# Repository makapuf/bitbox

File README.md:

bitbox
======

This is the core project for revision 2 bitbox.

Bitbox is a 32bit open hardware/source DIY console based on a unique chip (a cortex m4 with 1MB flash and 192k RAM).
It has 2 USB devices input, stereo sound output, micro SD card, VGA graphics up to 800x600 @ 32k colors. On the software side, a bootloader, simulators and several games, emulators and libraries.

Also the hardware is included here.

More info on [the development blog](http://bitboxconsole.blogspot.com)

Information can be found on [the project wiki](https://github.com/makapuf/bitbox/wiki)

You can also hop on the mailing list : bitbox-console@googlegroups.com  / https://groups.google.com/forum/#!forum/bitbox-console

Other repos
=========

This repository include the base SDK and some examples. There are other repos on github however: 

 * [A jumper game](https://github.com/makapuf/bitbox-jump)
 * [A GameBoy emulator](https://github.com/makapuf/bitboy)
 * [A ZX Spectrum 48 emulator](https://github.com/makapuf/bitbox-spectrum)
 * [Another game](https://github.com/makapuf/bitbox-polar)
 * [A sound toy / Rhythm box](https://github.com/makapuf/beatblocks)
 * [beam racer - a car game (WIP)](https://github.com/pulkomandy/beamracer_btbx)
 
... and many more ! See [the software index](https://github.com/makapuf/bitbox/wiki/Software-Index) on the wiki
makapuf

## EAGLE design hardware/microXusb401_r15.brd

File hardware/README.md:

hardware schematics and board licensed under the CC BY SA NC license.
please contact me for commercial uses

makapuf2@gmail.com

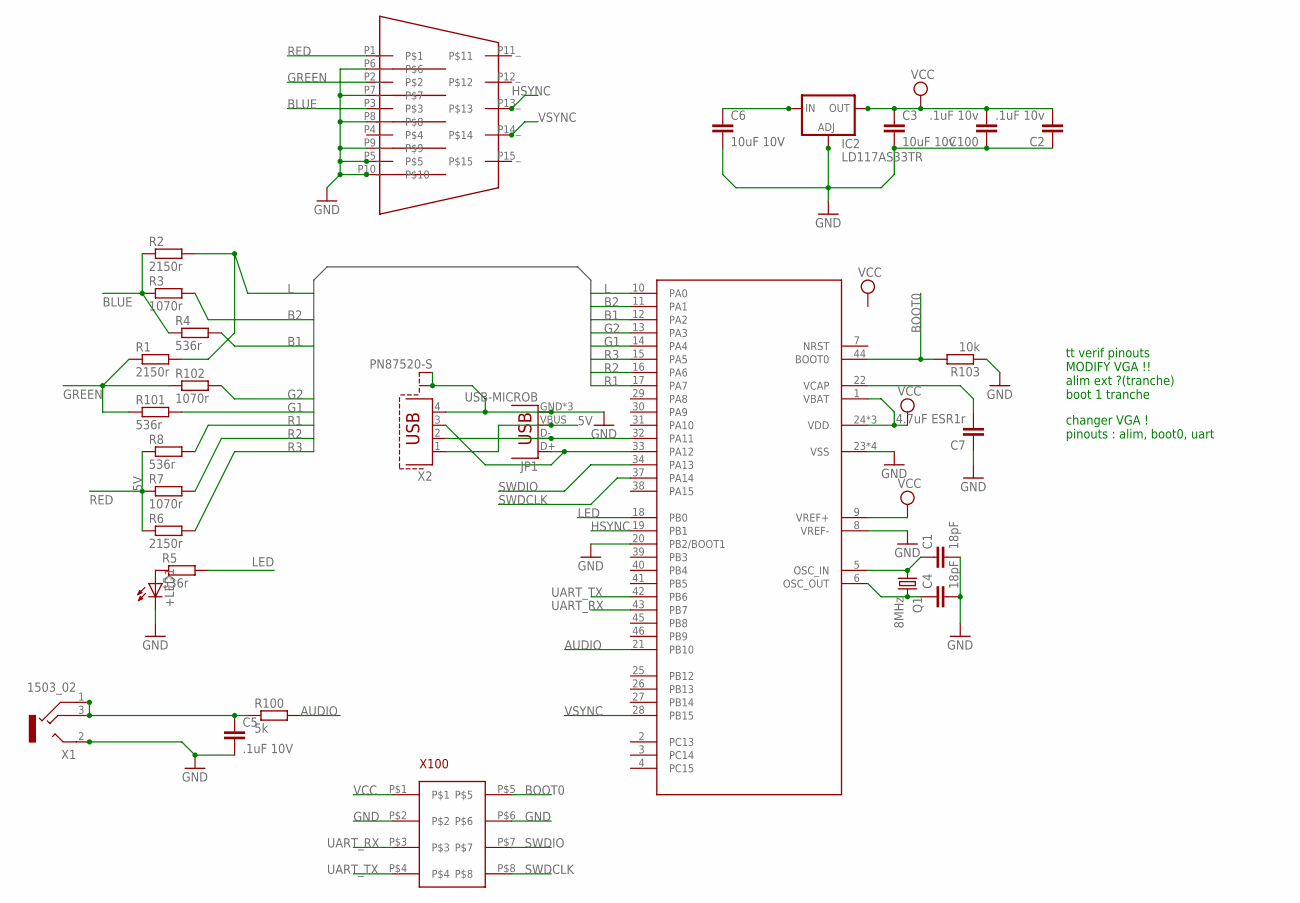
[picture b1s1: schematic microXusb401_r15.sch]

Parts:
+LED1: LEDCHIPLED_0805; CHIPLED_0805
C1, C4: 18pF; C1608
C2, C100: .1uF 10v; C1608
C3: 10uF 10v; C1608
C5: .1uF 10V; C1608
C6: 10uF 10V; C1608
C7: 4.7uF ESR1r; C1608
CON1: VGA_GTK_USLIM; VGA_SLIM3
IC1: STM32F401CCUQFN48_B; QFN-48
IC2: LD117AS33TR; SOT223
JP1: USB-MICROB
Q1: 8MHz; SM49
R1, R2, R6: 2150r; R0603
R3, R7, R102: 1070r; R0603
R4, R5, R8, R101: 536r; R0603
R100: 5k; R0603
R103: 10k; R0603
X1: 1503_02
X2: PN87520-S
X100: HEADER_BORDER_4X2

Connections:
5V: C6.1, IC2.3 (IN), JP1.VBUS, X2.1
AUDIO: IC1.21 (PB10), R100.2
B1: IC1.12 (PA2), R4.2
B2: IC1.11 (PA1), R3.2
BLUE: CON1.P3_, R2.1, R3.1, R4.1
BOOT0: IC1.44 (BOOT0), R103.2, X100.P$5
G1: IC1.14 (PA4), R101.2
G2: IC1.13 (PA3), R102.2
GND: +LED1.C, C1.2, C2.1, C3.2, C4.2, C5.2, C6.2, C7.1, C100.1, CON1.P5_, CON1.P6_, CON1.P7_, CON1.P8_, CON1.P9_, CON1.P10_, IC1.8 (VREF-), IC1.20 (PB2/BOOT1), IC1.23 (VSS), IC1.35 (VSS), IC1.47 (VSS), IC1.EXP (VSS), IC2.1 (ADJ), JP1.GND, JP1.MT1 (GND), JP1.MT2 (GND), R103.1, X1.2, X2.4, X2.S1, X2.S2, X100.P$2, X100.P$6
GREEN: CON1.P2_, R1.1, R101.1, R102.1
HSYNC: CON1.P13_, IC1.19 (PB1)
L: IC1.10 (PA0), R1.2, R2.2
LED: IC1.18 (PB0), R5.2
unnamed: IC1.33 (PA12), JP1.D+, X2.3
unnamed: IC1.32 (PA11), JP1.D-, X2.2
unnamed: C7.2, IC1.22 (VCAP)
unnamed: C5.1, R100.1, X1.1, X1.3
unnamed: +LED1.A, R5.1
unnamed: C1.1, IC1.5 (OSC_IN), Q1.1
unnamed: C4.1, IC1.6 (OSC_OUT), Q1.2
R1: IC1.17 (PA7), R8.2
R2: IC1.16 (PA6), R7.2
R3: IC1.15 (PA5), R6.2
RED: CON1.P1_, R6.1, R7.1, R8.1
SWDCLK: IC1.37 (PA14), X100.P$8
SWDIO: IC1.34 (PA13), X100.P$7
UART_RX: IC1.43 (PB7), X100.P$3
UART_TX: IC1.42 (PB6), X100.P$4
VCC: C2.2, C3.1, C100.2, IC1.1 (VBAT), IC1.9 (VREF+), IC1.24 (VDD), IC1.36 (VDD), IC1.48 (VDD), IC2.4 (OUT), X100.P$1
VSYNC: CON1.P14_, IC1.28 (PB15)

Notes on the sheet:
changer VGA ! pinouts : alim, boot0, uart
tt verif pinouts MODIFY VGA !! alim ext ?(tranche) boot 1 tranche

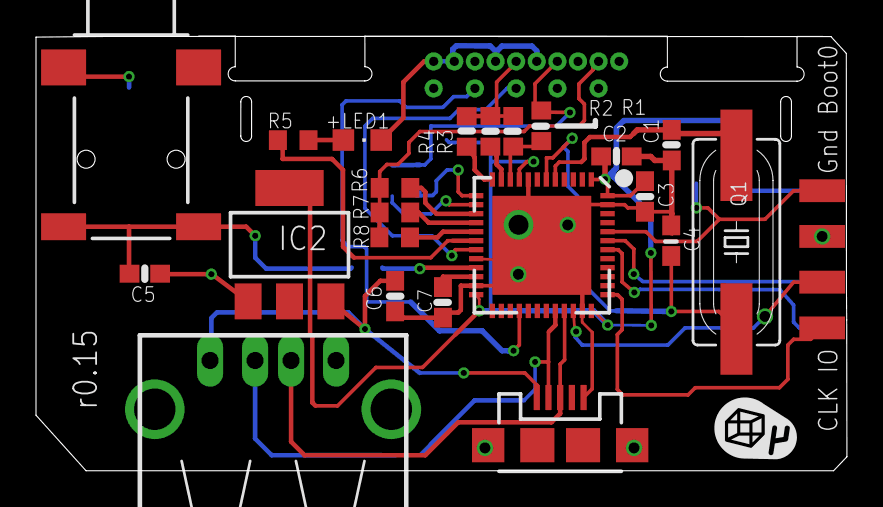
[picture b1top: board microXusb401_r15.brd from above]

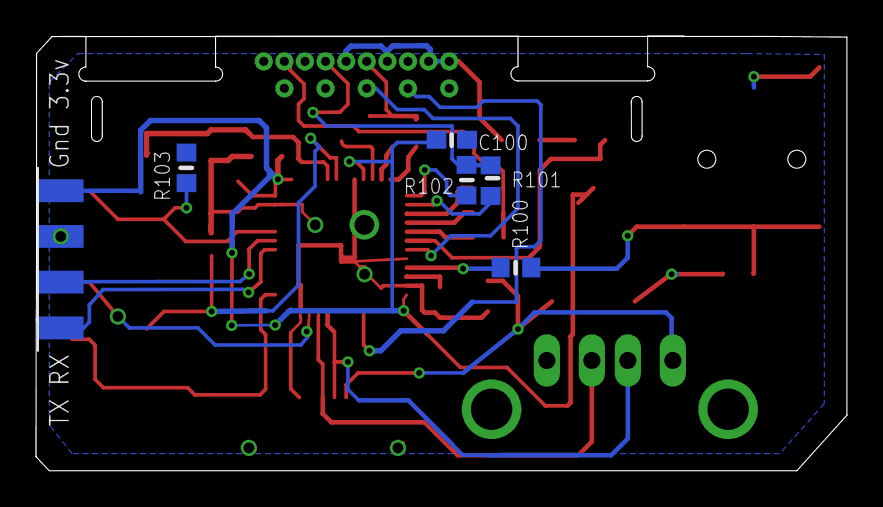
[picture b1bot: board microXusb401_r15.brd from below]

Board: 2 copper layers, 45.0 x 24.1 mm, 29 parts (6 on the bottom side), 30 nets.

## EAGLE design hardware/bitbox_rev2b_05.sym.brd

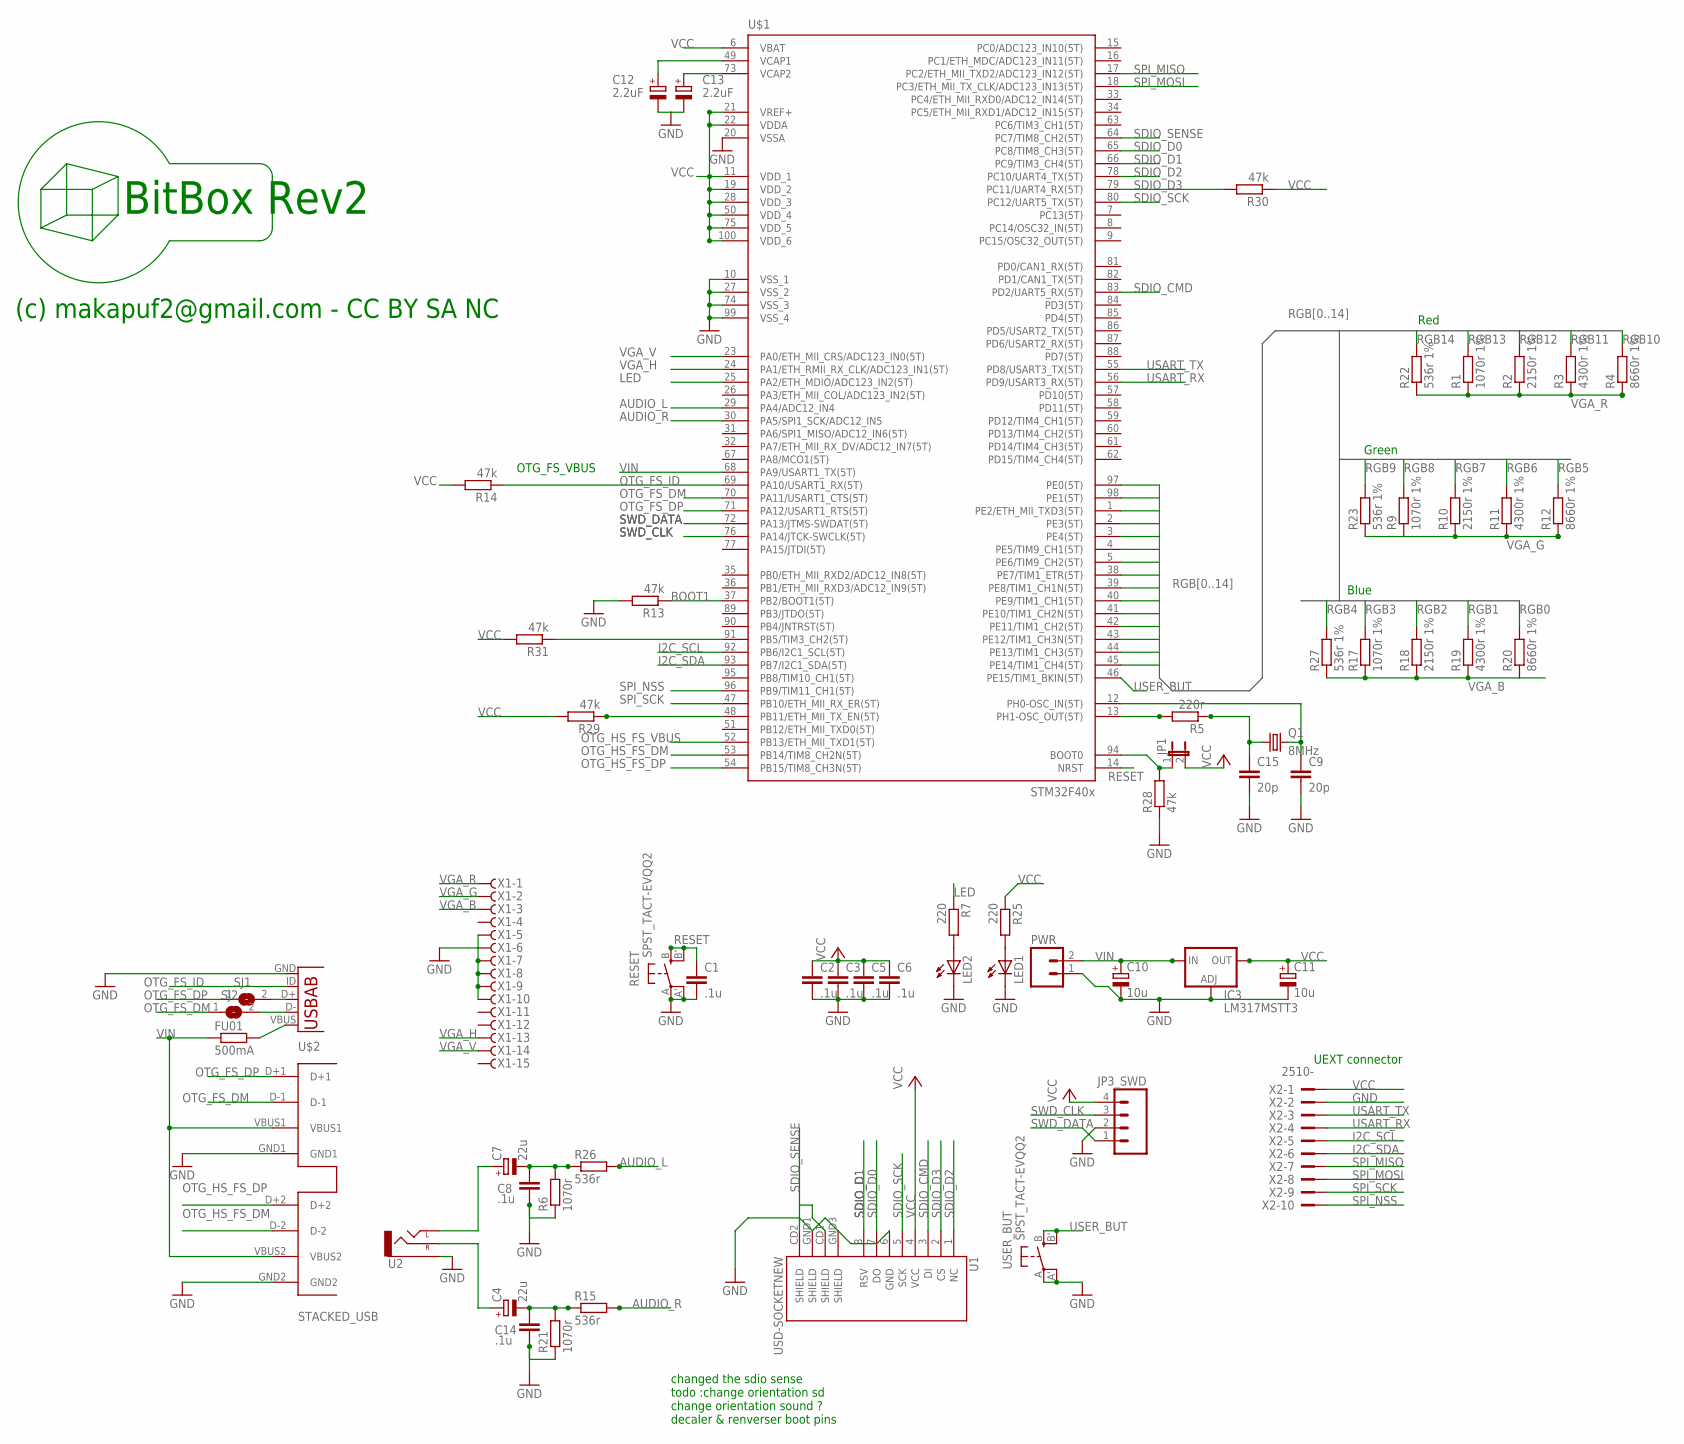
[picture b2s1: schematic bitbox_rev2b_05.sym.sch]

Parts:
C1, C2, C3, C5, C6, C8, C14: .1u; C0603
C4, C7: 22u; 153CLV-0505
C9, C15: 20p; C0603
C10, C11: 10u; SMC_A
C12, C13: 2.2uF; SMC_A
FU01: 500mA; R1206
IC3: LM317MSTT3; SOT223
JP1: JP1E; JP1
JP3_SWD: M04PTH; 1X04
LED1, LED2: LEDCHIPLED_0805; CHIPLED_0805
PWR: M02PTH; 1X02
Q1: 8MHz; SM49
R1, R9, R17: 1070r 1%; R0603
R2, R10, R18: 2150r 1%; R0603
R3, R11, R19: 4300r 1%; R0603
R4, R12, R20: 8660r 1%; R0603
R5: 220r; R0603
R6, R21: 1070r; R0603
R7, R25: 220; R0603
R13, R14, R28, R29, R30, R31: 47k; R0603
R15, R26: 536r; R0603
R22, R23, R27: 536r 1%; R0603
RESET: SPST_TACT-EVQQ2; EVQ-Q2
SJ1, SJ2: SJ
U1: USD-SOCKETNEW; MICRO-SD-SOCKET-PP
U2: AUDIO-JACKPTH; AUDIO-JACK
U3: USB-AB; USB-AB-MICRO-SMD
U$1: STM32F407V; TQFP100
U$2: STACKED_USB; 2STACKED
USER_BUT: SPST_TACT-EVQQ2; EVQ-Q2
X1: HF15HS; HDF15H
X2: 2510-; PAK100/2500-10

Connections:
AUDIO_L: R26.2, U$1.29 (PA4/ADC12_IN4)
AUDIO_R: R15.2, U$1.30 (PA5/SPI1_SCK/ADC12_IN5)
BOOT1: R13.1, U$1.37 (PB2/BOOT1(5T))
GND: C1.2, C2.2, C3.2, C5.2, C6.2, C8.2, C9.2, C10.-, C11.-, C12.-, C13.-, C14.2, C15.2, IC3.1 (ADJ), JP3_SWD.2, LED1.C, LED2.C, PWR.1, R6.1, R13.2, R21.1, R28.1, RESET.A, RESET.A' (P1), U1.6 (GND), U1.GND1 (SHIELD), U1.GND3 (SHIELD), U2.SLEEVE, U3.GND, U$1.10 (VSS_1), U$1.20 (VSSA), U$1.27 (VSS_2), U$1.74 (VSS_3), U$1.99 (VSS_4), U$2.GND1, U$2.GND2, USER_BUT.A, USER_BUT.A' (P1), X1.5, X1.6, X1.7, X1.8, X1.9, X1.10, X2.2
I2C_SCL: U$1.92 (PB6/I2C1_SCL(5T)), X2.5
I2C_SDA: U$1.93 (PB7/I2C1_SDA(5T)), X2.6
LED: R7.1, U$1.25 (PA2/ETH_MDIO/ADC123_IN2(5T))
unnamed: LED2.A, R7.2
unnamed: C13.+, U$1.73 (VCAP2)
unnamed: C7.+, U2.TIP (LEFT)
unnamed: C12.+, U$1.49 (VCAP1)
unnamed: SJ1.2, U3.D+
unnamed: C15.1, Q1.1, R5.1
unnamed: C9.1, Q1.2, U$1.12 (PH0-OSC_IN(5T))
unnamed: C4.-, C14.1, R15.1, R21.2
unnamed: C7.-, C8.1, R6.2, R26.1
unnamed: C4.+, U2.RING (RIGHT)
unnamed: FU01.2, U3.VBUS
unnamed: SJ2.2, U3.D-
unnamed: R31.1, U$1.91 (PB5/TIM3_CH2(5T))
unnamed: LED1.A, R25.2
unnamed: R5.2, U$1.13 (PH1-OSC_OUT(5T))
unnamed: JP1.1, R28.2, U$1.94 (BOOT0)
OTG_FS_DM: SJ2.1, U$1.70 (PA11/USART1_CTS(5T)), U$2.D-1
OTG_FS_DP: SJ1.1, U$1.71 (PA12/USART1_RTS(5T)), U$2.D+1
OTG_FS_ID: R14.1, U3.ID (USBID), U$1.69 (PA10/USART1_RX(5T))
OTG_HS_FS_DM: U$1.53 (PB14/TIM8_CH2N(5T)), U$2.D-2
OTG_HS_FS_DP: U$1.54 (PB15/TIM8_CH3N(5T)), U$2.D+2
OTG_HS_FS_VBUS: U$1.52 (PB13/ETH_MII_TXD1(5T))
RESET: C1.1, RESET.B (S), RESET.B' (S1), U$1.14 (NRST)
RGB0: R20.2, U$1.97 (PE0(5T))
RGB1: R19.2, U$1.98 (PE1(5T))
RGB2: R18.2, U$1.1 (PE2/ETH_MII_TXD3(5T))
RGB3: R17.2, U$1.2 (PE3(5T))
RGB4: R27.2, U$1.3 (PE4(5T))
RGB5: R12.2, U$1.4 (PE5/TIM9_CH1(5T))
RGB6: R11.2, U$1.5 (PE6/TIM9_CH2(5T))
RGB7: R10.2, U$1.38 (PE7/TIM1_ETR(5T))
RGB8: R9.2, U$1.39 (PE8/TIM1_CH1N(5T))
RGB9: R23.2, U$1.40 (PE9/TIM1_CH1(5T))
RGB10: R4.2, U$1.41 (PE10/TIM1_CH2N(5T))
RGB11: R3.2, U$1.42 (PE11/TIM1_CH2(5T))
RGB12: R2.2, U$1.43 (PE12/TIM1_CH3N(5T))
RGB13: R1.2, U$1.44 (PE13/TIM1_CH3(5T))
RGB14: R22.2, U$1.45 (PE14/TIM1_CH4(5T))
SDIO_CMD: U1.3 (DI), U$1.83 (PD2/UART5_RX(5T))
SDIO_D0: U1.7 (DO), U$1.65 (PC8/TIM8_CH3(5T))
SDIO_D1: U1.8 (RSV), U$1.66 (PC9/TIM3_CH4(5T))
SDIO_D2: U1.1 (NC), U$1.78 (PC10/UART4_TX(5T))
SDIO_D3: R30.2, U1.2 (CS), U$1.79 (PC11/UART4_RX(5T))
SDIO_SCK: U1.5 (SCK), U$1.80 (PC12/UART5_TX(5T))
SDIO_SENSE: U1.CD1 (SHIELD), U1.CD2 (SHIELD), U$1.64 (PC7/TIM8_CH2(5T))
SPI_MISO: U$1.17 (PC2/ETH_MII_TXD2/ADC123_IN12(5T)), X2.7
SPI_MOSI: U$1.18 (PC3/ETH_MII_TX_CLK/ADC123_IN13(5T)), X2.8
SPI_NSS: U$1.96 (PB9/TIM11_CH1(5T)), X2.10
SPI_SCK: U$1.47 (PB10/ETH_MII_RX_ER(5T)), X2.9
SWD_CLK: JP3_SWD.3, U$1.76 (PA14/JTCK-SWCLK(5T))
SWD_DATA: JP3_SWD.1, U$1.72 (PA13/JTMS-SWDAT(5T))
USART_RX: U$1.56 (PD9/USART3_RX(5T)), X2.4
USART_TX: U$1.55 (PD8/USART3_TX(5T)), X2.3
USER_BUT: U$1.46 (PE15/TIM1_BKIN(5T)), USER_BUT.B (S), USER_BUT.B' (S1)
VCC: C2.1, C3.1, C5.1, C6.1, C11.+, IC3.4 (OUT), JP1.2, JP3_SWD.4, R14.2, R25.1, R29.2, R30.1, R31.2, U1.4 (VCC), U$1.6 (VBAT), U$1.11 (VDD_1), U$1.19 (VDD_2), U$1.21 (VREF+), U$1.22 (VDDA), U$1.28 (VDD_3), U$1.50 (VDD_4), U$1.75 (VDD_5), U$1.100 (VDD_6), X2.1
VGA_B: R17.1, R18.1, R19.1, R20.1, R27.1, X1.3
VGA_G: R9.1, R10.1, R11.1, R12.1, R23.1, X1.2
VGA_H: U$1.24 (PA1/ETH_RMII_RX_CLK/ADC123_IN1(5T)), X1.13
VGA_R: R1.1, R2.1, R3.1, R4.1, R22.1, X1.1
VGA_V: U$1.23 (PA0/ETH_MII_CRS/ADC123_IN0(5T)), X1.14
VIN: C10.+, FU01.1, IC3.3 (IN), PWR.2, U$1.68 (PA9/USART1_TX(5T)), U$2.VBUS1, U$2.VBUS2
YYY: R29.1, U$1.48 (PB11/ETH_MII_TX_EN(5T))

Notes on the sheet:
Red
Green
Blue
UEXT connector
OTG_FS_VBUS
BitBox Rev2
(c) makapuf2@gmail.com - CC BY SA NC
changed the sdio sense todo :change orientation sd change orientation sound ? decaler & renverser boot pins

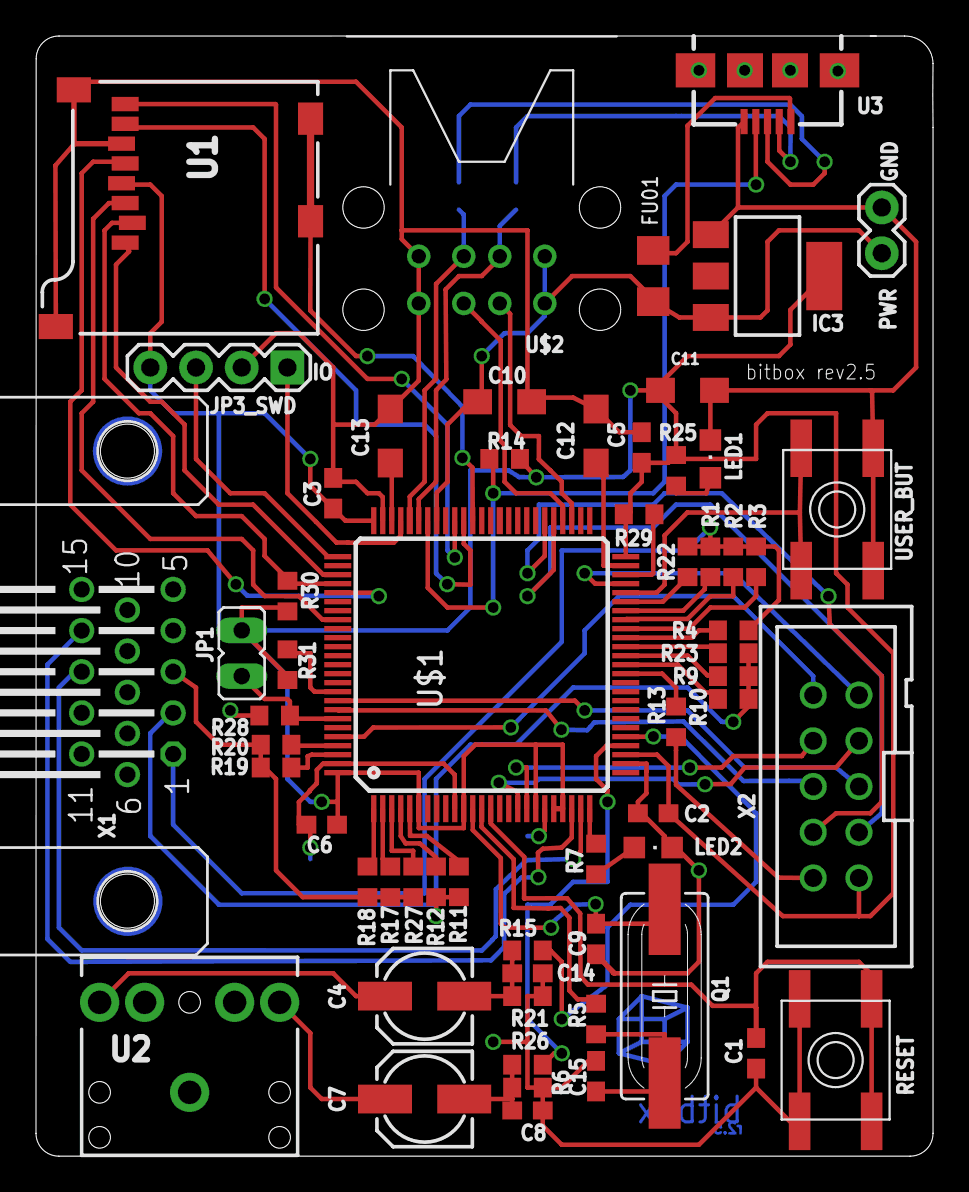
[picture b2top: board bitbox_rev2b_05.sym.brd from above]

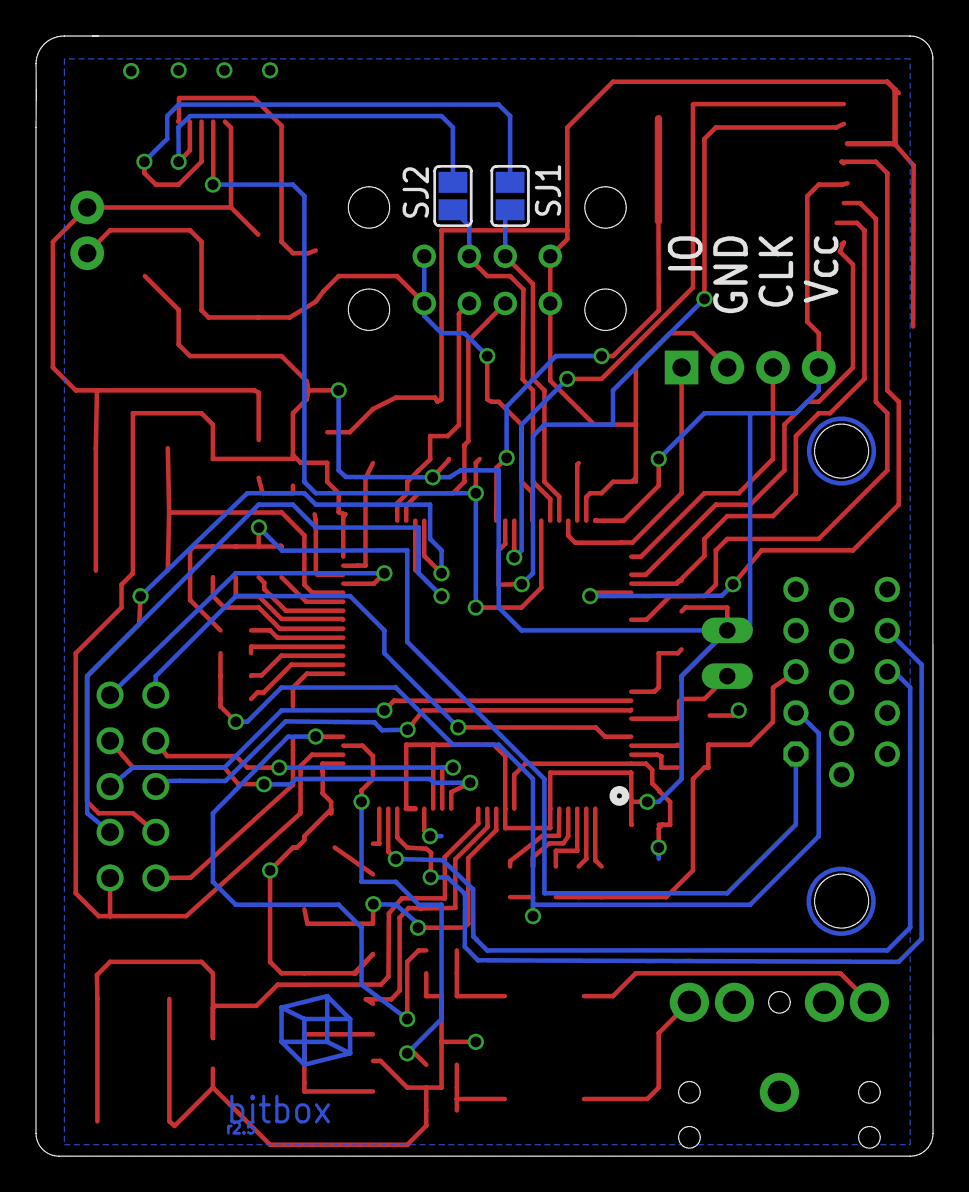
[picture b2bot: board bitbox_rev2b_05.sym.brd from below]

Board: 2 copper layers, 49.8 x 62.2 mm, 62 parts (2 on the bottom side), 68 nets.

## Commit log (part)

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2015-12-14 test_sdio readme
2015-12-14 fix remove song if not exist in test_chip
2015-12-14 re-added rcc.h
2015-12-14 typo on VGA_V_xxx
2015-12-14 make BITBOX var absolute in bibtox.mk
2015-12-14 fix cmsis file change for micro
2015-12-15 fix tester regarding pixel_t
2015-12-17 fixup! updated tmx
2015-12-19 adapted crappy for 8bit kernel
2015-12-20 changed palette_flash to initial_palette to avoid name clash
2015-12-21 removed small duplicate def
2015-12-21 convert tester to new kernel interface
2015-12-26 crappy : remove audio dependency
2015-12-26 commented out possibly unnecessary gamepad specification
2015-12-26 added a dfu-util option in makefile
2015-12-26 better names for new chiptune functions/methods
2015-12-26 fixed inlines to static inlines to suit c99
2015-12-26 allowing chip notes to be played even when a song isn't playing
2016-01-03 exported frames should be based from local ids
2016-01-03 additional tmx export fix
2016-01-03 allows decoding in sprite_encode2
2016-01-09 updated 2nd boot
    embed default icon
2016-01-10 Fix USB HS bug
    This was due to setting wrong Alternate Function ID ! (Datasheet
    STM32F405 p62).
    Fixes #45
2016-01-10 Added 15kHz PAL modes !
2016-01-11 Fix build for PAL target.
2016-01-11 Add some comments on the video signal details for PAL.
2016-01-11 2nd_boot: make it PAL compatible
    The reduced resolution requires some layout adjustments. Kept the same
    width for now, but it would be wise to reduce it a bit to get a less
    stretched font (or use a 8x8 font).
2016-01-11 moved VSYNC defs into board specific confs
2016-01-11 Improve export sprites and data in tmx.py
2016-01-11 allows blitter engine to start supporting 8bit out
2016-01-11 Fix tmx : enums dont need an = sign
2016-01-11 avoid name clashes in tmx.py
2016-01-12 test_chip: explicitly run script with Python
    - This works even when Python is not in /usr/bin (for example on Haiku).
2016-01-12 Add some helper target to compile for each target
    - Now you can "make pal" to make the PAL version of a project, no need
    to guess the exact filename.
    - Add 'phony' targets declaration, so if you have a file named "test",
    "clean", "pal", ... in your project, it won't break anything.
2016-01-13 added u8 sprites for 8bit modes
    and fix sprite export
2016-01-13 tmx update
    Fix off by one in property map offset
    Fix formatting of sprite types
    Fix : type order was not respected
2016-01-13 default output of decoded sprites is OFF
2016-01-13 changed VGAMODE_NONE to NO_VGA
    fixes #50
2016-01-13 Adjust "simple" modes for PAL platform
    - It is not possible to get exactly the same resolution, so we use the
    same font, and try to get a "similar" vertical resolution (adjusted to
    combinations that actually work, I guess it depends on the available
    CPU time).
    - The vertical resolution is always 271 pixels, which gives quite a low
    resolution with a 8x16 font. It works well with 6x8 and 8x8 fonts,
2016-01-13 allows several object layers
2016-01-20 Made changes to enable compilation on Mac OS X with Clang
2016-01-22 Added -dead_strip option for OS X builds (Clang version of -gc-sections)
2016-01-23 enabled fast skips
2016-01-23 make debugging info in chiptune engine optional
2016-01-25 revert $(NAME)_emu to $(NAME) for host target
2016-02-25 add bitbox micro eagle files
2016-03-04 shuffled init code
2016-03-07 use generic stm32f40_41 header
2016-03-07 put sdl2 and sdl1 side by side in emulator.c, try SDL2=1 in your Makefile
    currently no keyboard input works for SDL2, but scaling is nice.
2016-03-07 use CCM_MEMORY to specify variables in ccm
    Mac won't build without some extra stuff in the section string
2016-03-08 test kernel missing simple engine in makefile
2016-03-09 moved CCM to kconf, unified has CCM with CCM_memory
2016-03-11 fix:defines CCM_MEMORY as empty
    undefined as #define let the compiler mistake it for an identifer
2016-03-24 (emulator) allow pixel doubling
    also defaults to 32bit surfaces as its generally native and thus much
    faster.
2016-03-24 (emulator) now quiet by default. also changes commandline help
2016-04-11 dont align to 1024B line buffer since its expensive
2016-04-16 force signed char just to be sure
2016-04-23 make palette_flash weak
    so that default palette can be redefined for 8bit games on bitbox
2016-05-02 misc scripts improvements
2016-05-08 disallow dash / minus as allowed character in binary names
2016-05-10 (whitespace) alignments in makefile
2016-05-24 fixed simple mode 8
    thanks @lwagner !
2016-06-18 small bug : line8
    small bugfix : line8 shall be called instead of line by micro kernel
2016-06-18 updated simple modes
    implemented mode 13 for micro, also updated sample
2016-06-21 vgamicro is always a doubleline mode, so simplify it
2016-07-20 added back header auto dependecies
2016-07-28 Update .travis.yml
    small fix travis, updating to trusty tahr (14.04)
2016-07-28 Update .travis.yml
    replaced package python-imaging with python-pil
2016-07-28 Update .travis.yml
    added PIL import test
2016-07-28 Update .travis.yml
    PIL shouldn't be mentioned explicitely
2016-08-02 fixes for emulator file attributes (AM_DIR)
2016-09-23 emulator : hide mouse cursor and update help text
2016-09-23 test led now also tests button !
2016-09-30 adds pbc format (packbit couples)
2016-09-30 adds tile per row to fuzzy tile 2
2016-09-30 adds mkdata script
2016-10-01 first changes..
2016-10-01 renamed simple modes
2016-10-01 next updates to kernel, graph_frame -> graph_vsync
2016-10-01 fix emulator
2016-10-02 install pillow from pip
2016-10-03 set VGA_MODE to 320, 400 instead of N macros, explicit VGA_BPP
2016-10-03 fix tester
2016-10-03 tries to fix travis
2016-10-06 adds serial input/output (also emulated on stdout)
    will include buffers and async IOs
    should this be on kernel and allow message("xxx") to print to stdout
    anyway ?
2016-10-06 moving libs + examples in their own dirs
2016-10-06 backported L/R cmd on mac
2016-10-23 renamed demo to examples
2016-10-24 moved event to a lib
2016-10-24 moved pal micro to blitter script
2016-10-28 makefile fixes
2016-10-30 emulator didn't expand 8bpp last 2 pixels
2016-10-30 fix missing semicolon
2016-11-01 added image layer export option
2016-11-02 Adapt framebuffer library to 8bit kernels
2016-11-06 make keyboard events work with 2 usb
2016-11-08 fixed keys arrays
2016-11-09 makes crappy compatible with v0.10
2016-11-09 updated balls demo
2016-11-09 pbc now available for 16BPP also
2016-11-11 print_at: return number of printed chars
    print_at knows the number of printed char, and this can save a call to
    strlen. Part of my work to optimize screen redraw in the chiptracker.
2016-11-14 add return value to print_at (port from mainline)
2016-11-14 events.c reset mouse
2016-11-26 adds button operation for 2nd bootloader
2016-12-05 update tmap
2016-12-06 moved files
2016-12-06 simplified again
2016-12-06 removed device .h files, removed usb otg checks
2016-12-06 reformats
2016-12-07 changelog error fix (VGA_V_PIXELS) and graph_frame suggestion
    fix
2016-12-09 fix comment for lower vsync, "optimize" if/else if
2017-01-21 fix emulator file attributes when listing dir in dir
2017-01-21 Emulator: fix detection of directories.
    d_type causes more trouble than it solves…
    1) It is not part of POSIX standards: that only specifies an inode and a
    name
    (http://pubs.opengroup.org/onlinepubs/9699919799/basedefs/dirent.h.html).
    Anything else is platform specific.
    2) Even on Linux where this comes from, it is not supported by all
2017-01-22 Split the chiptune engine and make oscillators public again
    I really need to access them directly in the tracker, and I don't see a
    point in hiding them behind some hardware abstraction thing.
2017-01-22 Fix typo in changelog
2017-01-22 emulator: fix audio on Haiku.
    I found out that unsigned 8 bit audio does not work there.
2017-02-06 changed Uint to uint8_t in emulator
2017-02-06 add tinymalloc lib
2017-02-06 simplified makefiles, now needs submakes for making games
    This cleans the makefile greatly by splitting them between arm and posix
    compilations.
    For now the "old" bitbox.mk is kept but will eventually be discarded -
    or maybe kept as a compatibility stub then discarded.
2017-02-08 kconf typos
2017-02-19 Wording in audio logs
2017-02-19 moved flash emu to flashit in 2ndboot
2017-02-19 fix sampler makefile
2017-02-19 adds lto to bitbox arm compilation flags
2017-02-23 fixed binaries embedding in makefile, gitignore
2017-02-23 update tmx2
2017-03-06 fixes annoying warning in sdl
2017-03-06 small error in doc
2017-03-06 fixes unprintable 0x7f char
2017-03-10 minor lz4 changes
2017-03-10 updated chiptune : exposed internals for chiptracker
2017-03-10 updated typo in chiptracker
2017-03-10 chiptune make tbles extern
2017-03-11 Fix events key codes
2017-03-12 clean deletes output.map
2017-03-12 allows image exports in tmx.py / refactor a bit the code
2017-03-12 small fixes to embed.py
2017-03-13 fixed tmx
2017-03-13 use kconf emu VGA_V_SYNC
2017-03-26 add explicit errors in blitter tmap
2017-03-26 simplify handling of resources
    - now tinylz4 optionnally defines stream_uncompress but this will need
    t_malloc.
    - you can provide your own symbol to embed a file
2017-03-26 includes terrains in tmx
2017-04-06 allow NO_AUDIO to work under bitbox
2017-04-17 sdl backend defaults to 2x
2017-04-17 tmx2 exports types
2017-04-17 include guards for tsx exports
2017-04-17 less verbose tinymalloc
2017-04-17 tmap fixes
2017-05-08 added MOD file library
2017-05-09 reverted (temporarily) lto linking
2017-05-09 gamepad_x/y do do things
2017-05-11 tmx2 now generates the tileset with its orginial name (allowing sharing)
2017-05-16 remove PROFILE from crappy Makefile
2017-05-16 st-util should flash .bin not .elf, debug the contrary
2017-05-16 set defualt resolution of test to sth suitable for micro
2017-05-16 adds 4x6 font (first version, not all characters)
2017-05-18 updated crappy
    dithered gradient BG
    allow mouse buttons
    remove NOSDIO since it's now off by default
2017-05-20 Fix build and sound output on Haiku.
2017-05-20 Emulator: Fix enumerating the current directory as "".
    Chiptracker does this, and it works on real hardware.
    Replace it with "." in the emulator context.
2017-05-20 make crappy model independant
2017-05-20 vga bitbox did not show whole lines when emulating micro !
2017-05-20 8/16 bit fixes for textmodes
2017-05-21 updates testusb view of device status
2017-05-21 chiptracker: Add sinewaves
    Computed with a quick polynomial approximation.
    Also increase the internal precision of the chiptune engine, otherwise
    the phase modulation is a bit too grainy.
    The sinewave can be altered using the duty cycle (d and m effects in the
    tracker) to replicate most OPL2 waveforms, and more. use of vibrato and
    modulation can be used to get something not too far from a 4-operation
2017-05-28 tinylz4: hints how to encode lz4 files
2017-05-28 sdl : scale is 2 only when vertical size is less than 400
2017-05-28 vga_bitbox : changed pixel_t to uint16_t to avoid warnings when VGA_BPP=8
2017-06-12 enable rename in ffconf/sdl
2017-06-12 disable micro defaulting to 8bpp will need to be explicitely defined now
2017-06-12 testusb : avoid warnings
2017-07-04 reinit keyb event structure in events lib
    key struct was not reinitialized properly and was an error
    Fixes #89
2017-07-13 support for long file names, also in emulator
2017-07-25 update LFN support for boot2
2017-07-25 adds control transfer status to test usb
2017-07-28 init sprite3
2017-08-21 Add nb transfers info on usb test
    Now with more debug info
2017-08-24 added color icons, integrated to .bin files
2017-09-01 allow update values for sound in bitbox_kconf
2017-09-01 fixed makefile
2017-09-07 update 2ndboot display
    - make flashit.c a flash ony program and dont update the display
    - make 2ndboot display all errors
    - make second boot not halt when finished
    - adds a small description text after the icon (4 lines of 32chars fixed
    size)
    - mk icon has been changed to generate texts (from png comment) and
2017-09-07 smell duplicate makes gcc crash ?
2017-09-10 make mk ic accept palette images with old versions of pil
2017-10-04 update sprite3 and mk_spr
    This creates a new version of the sprite blitter. it will eventually
    replace all the sprite_xxx.py scripts mess.
2017-10-12 make 2ndboot stop when flashed (flash with button)
2017-10-14 allow output directory for tsx output
2017-11-03 add size field in sdl ff implementation
2017-11-03 mk_spr : encode hitbox and avoid getting more than 65535 back references
2017-11-03 allow removing known extensions from embed.py
2017-11-03 add nbframes to blitter
2017-11-03 removed SDK from this branch, use submodule
2017-11-03 remove other files
2017-11-03 updated sdk
2017-11-03 updated balls example to sprite3

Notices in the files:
parts and their libraries:
SparkFun-Connectors: Licensing: CC v3.0 Share-Alike You are welcome to use this library for commercial purposes.
